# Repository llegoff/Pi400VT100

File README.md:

[:fr:](LISEZMOI.md) [:uk:](README.md)

# Pi400VT100
VGA & Serial interface for Raspberry Pi 400

## DPI (Display parallel Interface)
Like [VGA666](https://github.com/fenlogic/vga666), this pcb uses dpi interface (in mode 7, and 3x4bits to free gpio 12 to 15)

see https://www.raspberrypi.org/documentation/hardware/raspberrypi/dpi/README.md

only the necessary bits of the dpi are redirected to the 40-pin GPIO port, with the 'gpio=2-3,8-11,16-19,24-27=a2' line on config.txt

/boot/config.txt
    
    # replace dtoverlay=vc4-kms-v3d with
    dtoverlay=vc4-fkms-v3d
    
    # disable i2c, pin use by h-sync & v-sync
    dtparam=i2c_arm=off
    gpio=2-3,8-11,16-19,24-27=a2
    dpi_output_format=0x17
    enable_dpi_lcd=1
    display_default_lcd=1
    dpi_group=2
    dpi_mode=16
    #---------------- dpi_mode line ---------------------
    #---> 640x480 60hz    dpi_mode=4
    #---> 800x600 60hz    dpi_mode=9
    #---> 1024x768 60hz   dpi_mode=16
    #---> 1280x768 60hz   dpi_mode=23
    #---> 1280x800 60hz   dpi_mode=28
    #---> 1280x960 60hz   dpi_mode=32
    #---> 1280x1024 60hz  dpi_mode=35
    #---> 1360x768 60hz   dpi_mode=39
    #---> 1366x768 60hz   dpi_mode=81
    #---> 1400x1050 60hz  dpi_mode=42
    #---> 1440x900 60hz   dpi_mode=47
    #---> 1600x1200 60hz  dpi_mode=51
    #---> 1680x1050 60hz  dpi_mode=58
    #---> 1920x1080 60hz  dpi_mode=82
    #---> 1920x1200 60hz  dpi_mode=69
    #---> 1920x1440 60hz  dpi_mode=73

## Serial port

    # Enable Uart /dev/ttyAMA1, on pin 12,13,14,15
    dtoverlay=uart5,ctsrts

## Schematic

## PCB

## Installation
copy content of [config-example.txt](img/config-example.txt?raw=true) to /boot/config.txt

install Minicom

    sudo apt update
    sudo apt upgrade
    sudo apt install minicom
    
run minicom with default config

    minicom -D /dev/ttyAMA1

run minicom 9600bps 8bit 

    minicom -b 9600 -8 -D /dev/ttyAMA1

## Révision
rev1
  bad space between VGA and DB9 connectors
  
rev2

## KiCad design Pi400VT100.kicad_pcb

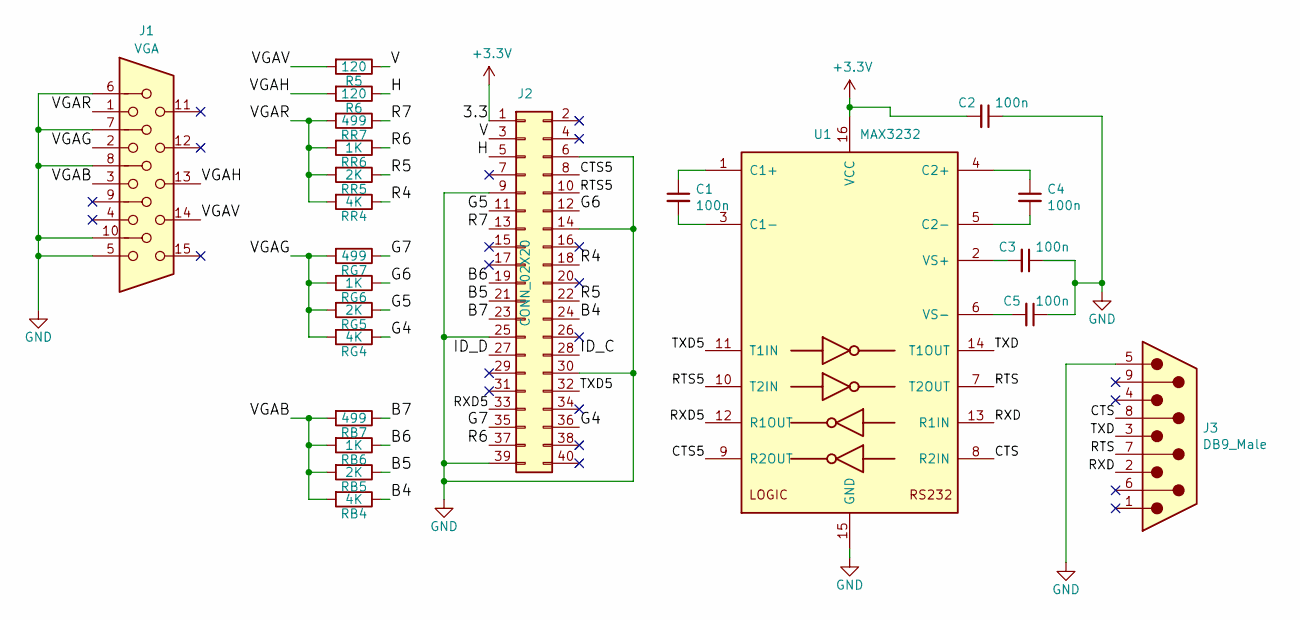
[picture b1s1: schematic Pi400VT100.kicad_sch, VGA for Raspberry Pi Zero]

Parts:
C1, C2, C3, C4, C5: 100n; C_0805
J1: VGA; DB_15F-VGA
J2: CONN_02X20; Socket_Strip_Straight_2x20_Pitch2.54mm
J3: DB9_Male; DB9MC
R5, R6: 120; R_0805
RB4: 4K; R_0805
RB5: 2K; R_0805
RB6: 1K; R_0805
RB7: 499; R_0805
RG4: 4K; R_0805
RG5: 2K; R_0805
RG6: 1K; R_0805
RG7: 499; R_0805
RR4: 4K; R_0805
RR5: 2K; R_0805
RR6: 1K; R_0805
RR7: 499; R_0805
U1: MAX3232; TSSOP-16_4.4x5mm_Pitch0.65mm

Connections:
+3V3: C2.2, J2.1, U1.16 (VCC)
/B4: J2.24, RB4.1
/B5: J2.21, RB5.1
/B6: J2.19, RB6.1
/B7: J2.23, RB7.1
/CTS: J3.8, U1.8 (R2IN)
/CTS5: J2.8, U1.9 (R2OUT)
/G4: J2.36, RG4.1
/G5: J2.11, RG5.1
/G6: J2.12, RG6.1
/G7: J2.35, RG7.1
/H: J2.5, R6.1
/ID_C: J2.28
/ID_D: J2.27
/R4: J2.18, RR4.1
/R5: J2.22, RR5.1
/R6: J2.37, RR6.1
/R7: J2.13, RR7.1
/RTS: J3.7, U1.7 (T2OUT)
/RTS5: J2.10, U1.10 (T2IN)
/RXD: J3.2, U1.13 (R1IN)
/RXD5: J2.33, U1.12 (R1OUT)
/TXD: J3.3, U1.14 (T1OUT)
/TXD5: J2.32, U1.11 (T1IN)
/V: J2.3, R5.1
/VGAB: J1.3, RB4.2, RB5.2, RB6.2, RB7.2
/VGAG: J1.2, RG4.2, RG5.2, RG6.2, RG7.2
/VGAH: J1.13, R6.2
/VGAR: J1.1, RR4.2, RR5.2, RR6.2, RR7.2
/VGAV: J1.14, R5.2
GND: C2.1, C3.1, C5.1, J1.5, J1.6, J1.7, J1.8, J1.10, J2.6, J2.9, J2.14, J2.25, J2.30, J2.39, J3.5, U1.15 (GND)
unnamed: C1.1, U1.1 (C1+)
unnamed: C1.2, U1.3 (C1-)
unnamed: C3.2, U1.2 (VS+)
unnamed: C4.1, U1.4 (C2+)
unnamed: C4.2, U1.5 (C2-)
unnamed: C5.2, U1.6 (VS-)

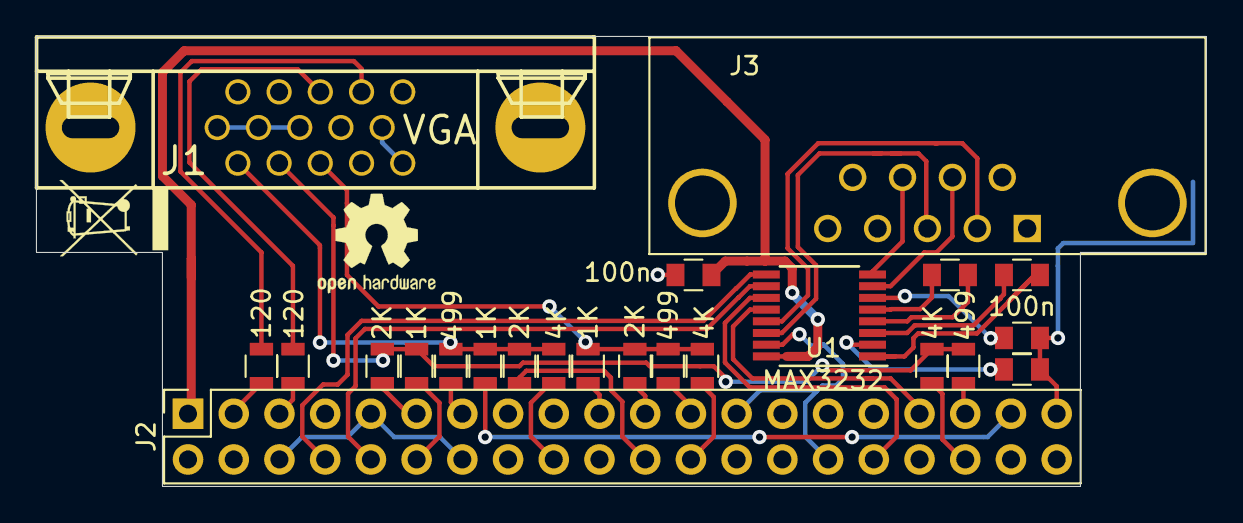
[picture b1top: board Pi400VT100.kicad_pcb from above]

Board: 2 copper layers, 65.0 x 25.0 mm, 23 parts (0 on the bottom side), 35 nets.

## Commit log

2022-03-01 Add files via upload
    V2
